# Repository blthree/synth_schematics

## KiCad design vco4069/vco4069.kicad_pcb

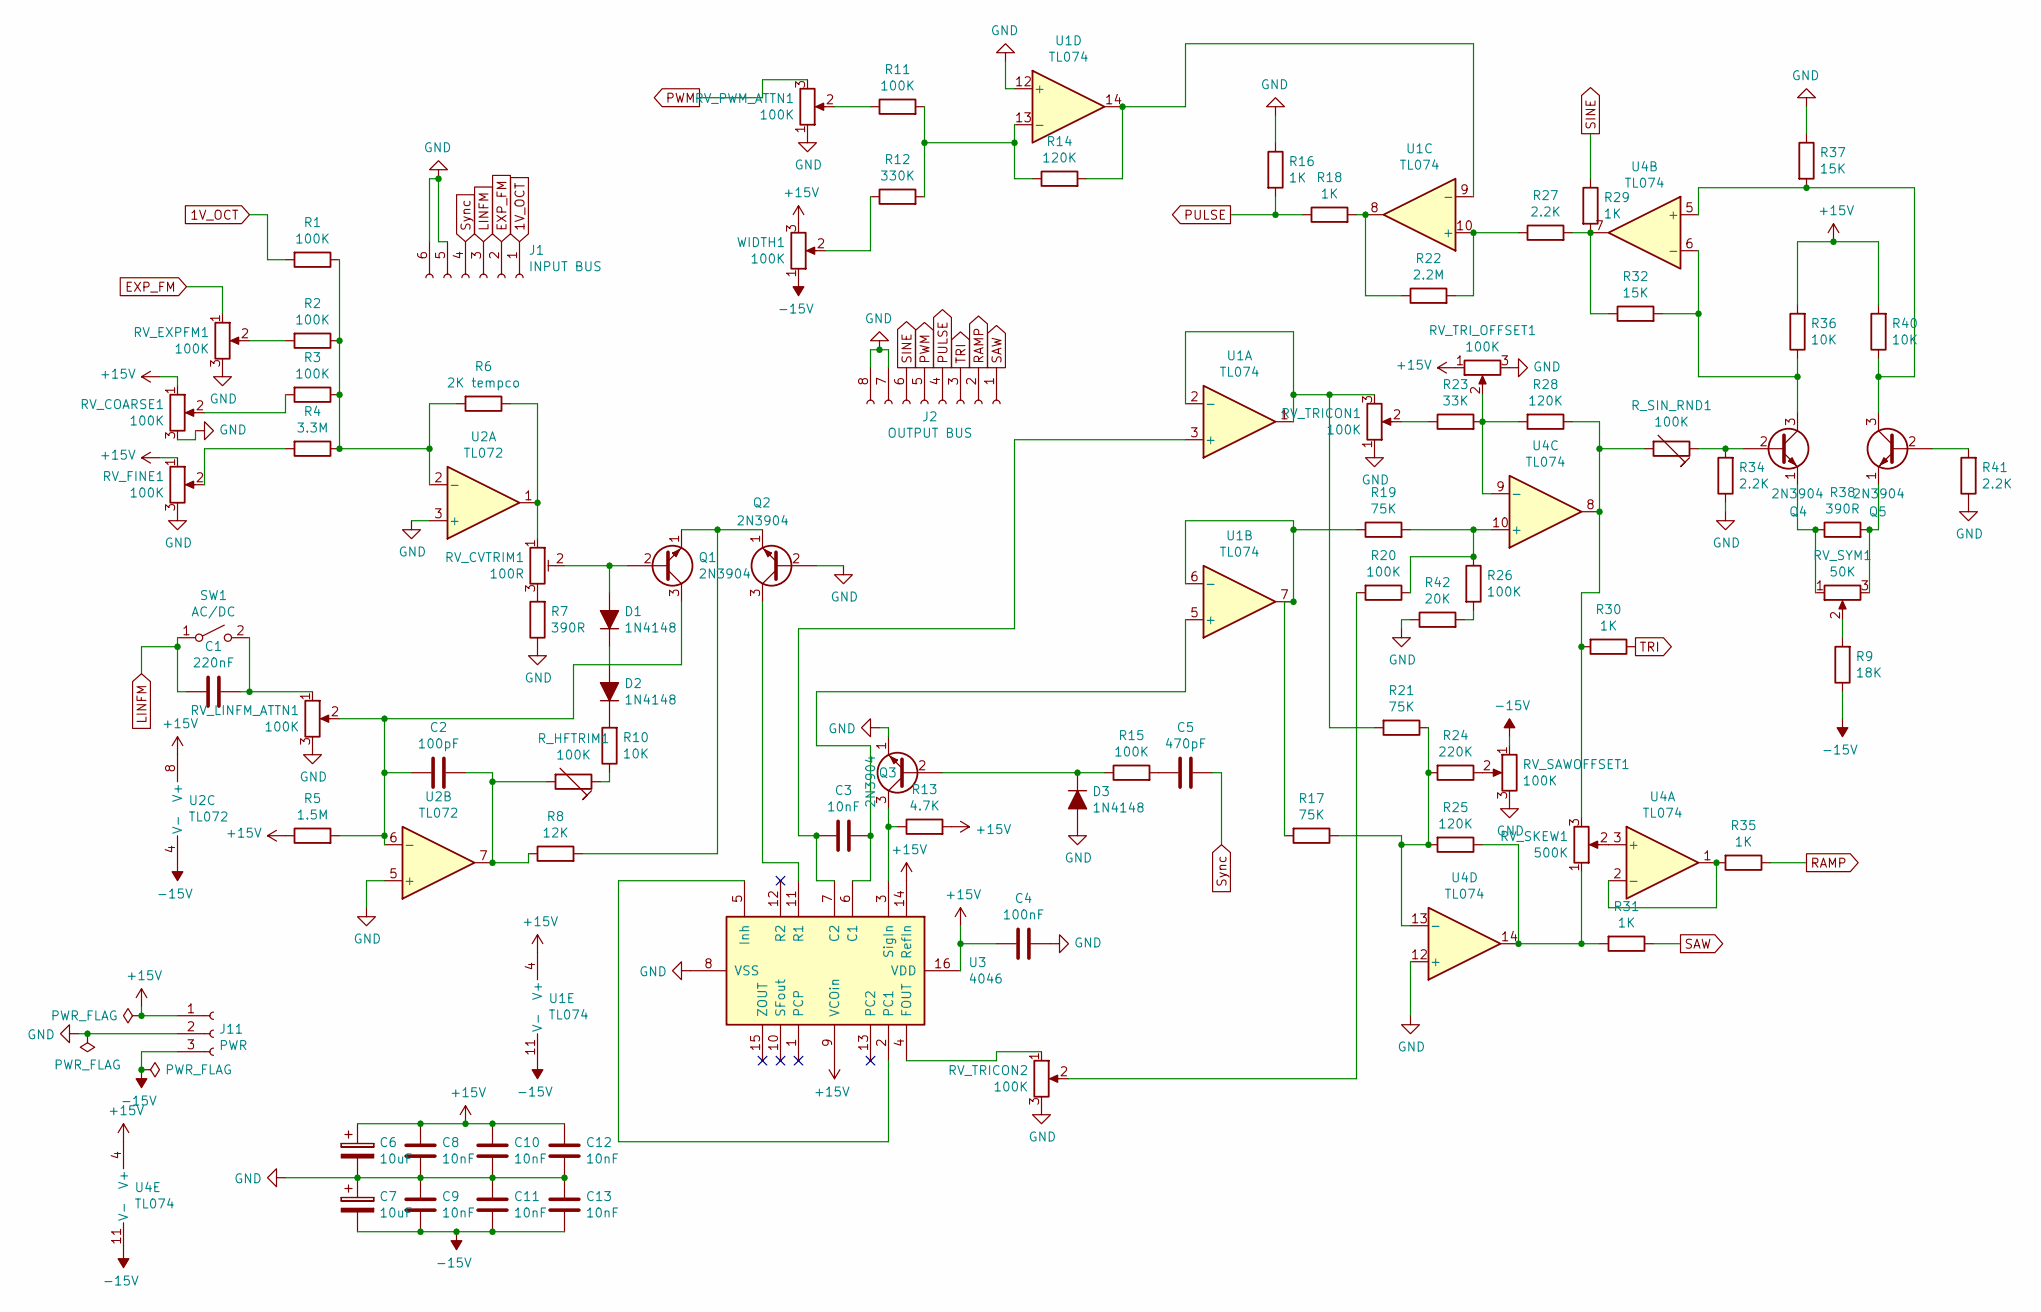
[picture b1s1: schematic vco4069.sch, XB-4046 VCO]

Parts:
C1: 220nF; C_Disc_D4.7mm_W2.5mm_P5.00mm
C2: 100pF; C_Disc_D4.7mm_W2.5mm_P5.00mm
C3, C8, C9, C10, C11, C12, C13: 10nF; C_Disc_D4.7mm_W2.5mm_P5.00mm
C4: 100nF; C_Disc_D4.7mm_W2.5mm_P5.00mm
C5: 470pF; C_Disc_D4.7mm_W2.5mm_P5.00mm
C6, C7: 10uF; CP_Radial_D10.0mm_P5.00mm
D1, D2, D3: 1N4148; D_DO-35_SOD27_P7.62mm_Horizontal
J1: INPUT BUS; PinHeader_1x06_P2.54mm_Vertical
J2: OUTPUT BUS; PinHeader_1x08_P2.54mm_Vertical
J11: PWR; PinHeader_1x03_P2.54mm_Vertical
Q1, Q2, Q3, Q4, Q5: 2N3904; TO-92_Inline
R1, R2, R3, R11, R15, R20, R26: 100K; R_Axial_DIN0207_L6.3mm_D2.5mm_P5.08mm_Vertical
R4: 3.3M; R_Axial_DIN0207_L6.3mm_D2.5mm_P5.08mm_Vertical
R5: 1.5M; R_Axial_DIN0207_L6.3mm_D2.5mm_P5.08mm_Vertical
R6: 2K tempco; R_Axial_DIN0207_L6.3mm_D2.5mm_P5.08mm_Vertical
R7, R38: 390R; R_Axial_DIN0207_L6.3mm_D2.5mm_P5.08mm_Vertical
R8: 12K; R_Axial_DIN0207_L6.3mm_D2.5mm_P5.08mm_Vertical
R9: 18K; R_Axial_DIN0207_L6.3mm_D2.5mm_P5.08mm_Vertical
R10, R36, R40: 10K; R_Axial_DIN0207_L6.3mm_D2.5mm_P5.08mm_Vertical
R12: 330K; R_Axial_DIN0207_L6.3mm_D2.5mm_P5.08mm_Vertical
R13: 4.7K; R_Axial_DIN0207_L6.3mm_D2.5mm_P5.08mm_Vertical
R14, R25, R28: 120K; R_Axial_DIN0207_L6.3mm_D2.5mm_P5.08mm_Vertical
R16, R18, R29, R30, R31, R35: 1K; R_Axial_DIN0207_L6.3mm_D2.5mm_P5.08mm_Vertical
R17, R19, R21: 75K; R_Axial_DIN0207_L6.3mm_D2.5mm_P5.08mm_Vertical
R22: 2.2M; R_Axial_DIN0207_L6.3mm_D2.5mm_P5.08mm_Vertical
R23: 33K; R_Axial_DIN0207_L6.3mm_D2.5mm_P5.08mm_Vertical
R24: 220K; R_Axial_DIN0207_L6.3mm_D2.5mm_P5.08mm_Vertical
R27, R34, R41: 2.2K; R_Axial_DIN0207_L6.3mm_D2.5mm_P5.08mm_Vertical
R32, R37: 15K; R_Axial_DIN0207_L6.3mm_D2.5mm_P5.08mm_Vertical
R42: 20K; R_Axial_DIN0207_L6.3mm_D2.5mm_P5.08mm_Vertical
RV_COARSE1: 100K; PinHeader_1x03_P2.54mm_Vertical
RV_CVTRIM1: 100R; Potentiometer_Bourns_3296Z_Horizontal
RV_EXPFM1: 100K; PinHeader_1x03_P2.54mm_Vertical
RV_FINE1: 100K; PinHeader_1x03_P2.54mm_Vertical
RV_LINFM_ATTN1: 100K; PinHeader_1x03_P2.54mm_Vertical
RV_PWM_ATTN1: 100K; PinHeader_1x03_P2.54mm_Vertical
RV_SAWOFFSET1: 100K; PinHeader_1x03_P2.54mm_Vertical
RV_SKEW1: 500K; PinHeader_1x03_P2.54mm_Vertical
RV_SYM1: 50K; Potentiometer_Bourns_3296W_Vertical
RV_TRICON1, RV_TRICON2: 100K; PinHeader_1x03_P2.54mm_Vertical
RV_TRI_OFFSET1: 100K; PinHeader_1x03_P2.54mm_Vertical
R_HFTRIM1: 100K; Potentiometer_Bourns_3296W_Vertical
R_SIN_RND1: 100K; Potentiometer_Bourns_3296W_Vertical
SW1: AC/DC; PinHeader_1x02_P2.54mm_Vertical
U1, U4: TL074; DIP-14_W7.62mm_Socket
U2: TL072; DIP-8_W7.62mm_Socket
U3: 4046; DIP-16_W7.62mm_Socket
WIDTH1: 100K; PinHeader_1x03_P2.54mm_Vertical

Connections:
1V_OCT: J1.1, R1.2
+15V: C4.2, C6.1, C8.2, C10.2, C12.2, J11.1, R5.1, R13.2, R36.2, R40.2, RV_COARSE1.1, RV_FINE1.1, RV_TRI_OFFSET1.1, U1.4 (V+), U2.8 (V+), U3.9 (VCOin), U3.14 (RefIn), U3.16 (VDD), U4.4 (V+), WIDTH1.3
-15V: C7.2, C9.1, C11.1, C13.1, J11.3, R9.1, RV_SAWOFFSET1.1, U1.11 (V-), U2.4 (V-), U4.11 (V-), WIDTH1.1
EXP_FM: J1.2, RV_EXPFM1.1
GND: C4.1, C6.2, C7.1, C8.1, C9.2, C10.1, C11.2, C12.1, C13.2, D3.2 (A), J1.5, J1.6, J2.7, J2.8, J11.2, Q2.2 (B), Q3.1 (E), R7.1, R16.1, R34.1, R37.1, R41.1, R42.1, RV_COARSE1.3, RV_EXPFM1.3, RV_FINE1.3, RV_LINFM_ATTN1.3, RV_PWM_ATTN1.1, RV_SAWOFFSET1.3, RV_TRICON1.1, RV_TRICON2.3, RV_TRI_OFFSET1.3, U1.12 (+), U2.3 (+), U2.5 (+), U3.8 (VSS), U4.12 (+)
LINFM: C1.2, J1.3, SW1.1 (A)
unnamed: C1.1, RV_LINFM_ATTN1.1, SW1.2 (B)
unnamed: C2.1, R8.1, R_HFTRIM1.2, U2.7
unnamed: C2.2, Q1.3 (C), R5.2, RV_LINFM_ATTN1.2, U2.6 (-)
unnamed: C3.1, U1.5 (+), U3.6 (C1)
unnamed: C3.2, U1.3 (+), U3.7 (C2)
unnamed: C5.2, R15.2
unnamed: D1.1 (K), D2.2 (A)
unnamed: D1.2 (A), Q1.2 (B), RV_CVTRIM1.2
unnamed: D2.1 (K), R10.2
unnamed: D3.1 (K), Q3.2 (B), R15.1
unnamed: Q1.1 (E), Q2.1 (E), R8.2
unnamed: Q2.3 (C), U3.11 (R1)
unnamed: Q3.3 (C), R13.1, U3.3 (SigIn)
unnamed: Q4.1 (E), R38.1, RV_SYM1.1
unnamed: Q4.2 (B), R34.2, R_SIN_RND1.1
unnamed: Q4.3 (C), R32.2, R36.1, U4.6 (-)
unnamed: Q5.1 (E), R38.2, RV_SYM1.3
unnamed: Q5.2 (B), R41.2
unnamed: Q5.3 (C), R37.2, R40.1, U4.5 (+)
unnamed: R1.1, R2.1, R3.1, R4.1, R6.2, U2.2 (-)
unnamed: R2.2, RV_EXPFM1.2
unnamed: R3.2, RV_COARSE1.2
unnamed: R4.2, RV_FINE1.2
unnamed: R6.1, RV_CVTRIM1.1, U2.1
unnamed: R7.2, RV_CVTRIM1.3
unnamed: R9.2, RV_SYM1.2
unnamed: R10.1, R_HFTRIM1.1
unnamed: R11.1, RV_PWM_ATTN1.2
unnamed: R11.2, R12.2, R14.1, U1.13 (-)
unnamed: R12.1, WIDTH1.2
unnamed: R14.2, U1.9 (-), U1.14
unnamed: R17.1, R21.1, R24.2, R25.2, U4.13 (-)
unnamed: R17.2, R19.1, U1.6 (-), U1.7
unnamed: R18.2, R22.1, U1.8
unnamed: R19.2, R20.1, R26.1, U4.10 (+)
unnamed: R20.2, RV_TRICON2.2
unnamed: R21.2, RV_TRICON1.3, U1.1, U1.2 (-)
unnamed: R22.2, R27.1, U1.10 (+)
unnamed: R23.1, RV_TRICON1.2
unnamed: R23.2, R28.2, RV_TRI_OFFSET1.2, U4.9 (-)
unnamed: R24.1, RV_SAWOFFSET1.2
unnamed: R25.1, R31.2, RV_SKEW1.1, U4.14
unnamed: R26.2, R42.2
unnamed: R27.2, R29.2, R32.1, U4.7
unnamed: R28.1, R30.2, RV_SKEW1.3, R_SIN_RND1.2, U4.8
unnamed: R35.2, U4.1, U4.2 (-)
unnamed: RV_SKEW1.2, U4.3 (+)
unnamed: RV_TRICON2.1, U3.4 (FOUT)
unnamed: U3.2 (PC1), U3.5 (Inh)
PULSE: J2.4, R16.2, R18.1
PWM: J2.5, RV_PWM_ATTN1.3
RAMP: J2.2, R35.1
SAW: J2.1, R31.1
SINE: J2.6, R29.1
Sync: C5.1, J1.4
TRI: J2.3, R30.1

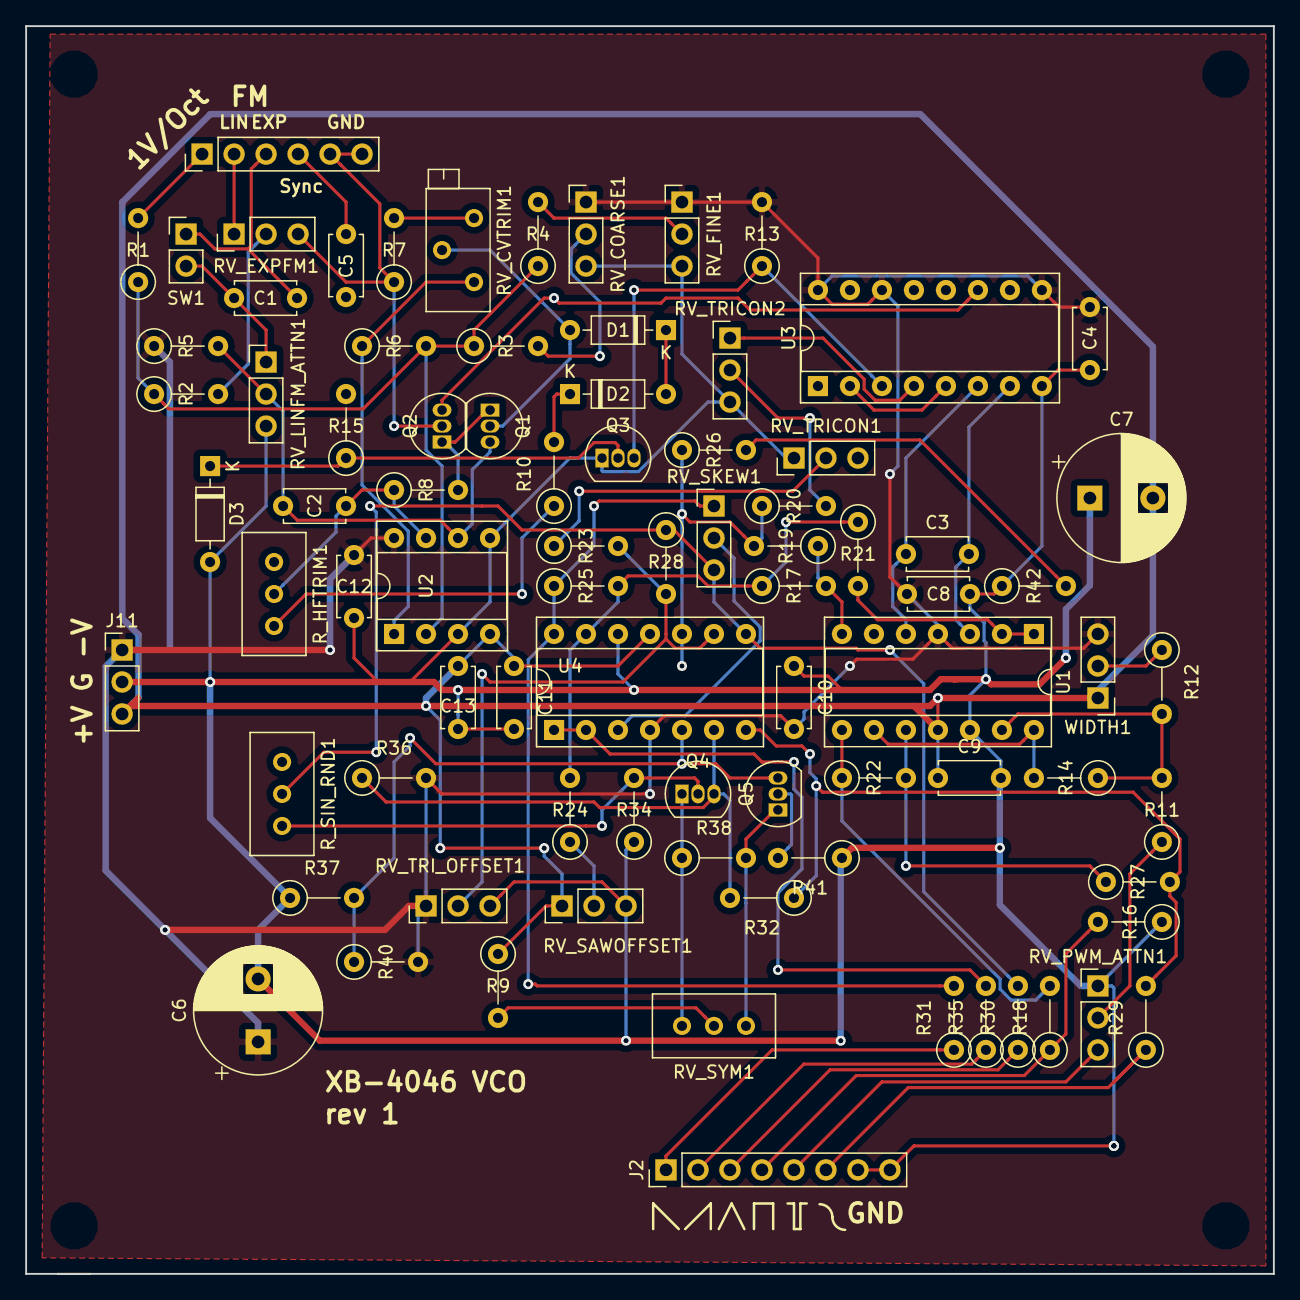
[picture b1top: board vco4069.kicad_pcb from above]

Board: 2 copper layers, 99.1 x 99.1 mm, 84 parts (0 on the bottom side), 62 nets.
